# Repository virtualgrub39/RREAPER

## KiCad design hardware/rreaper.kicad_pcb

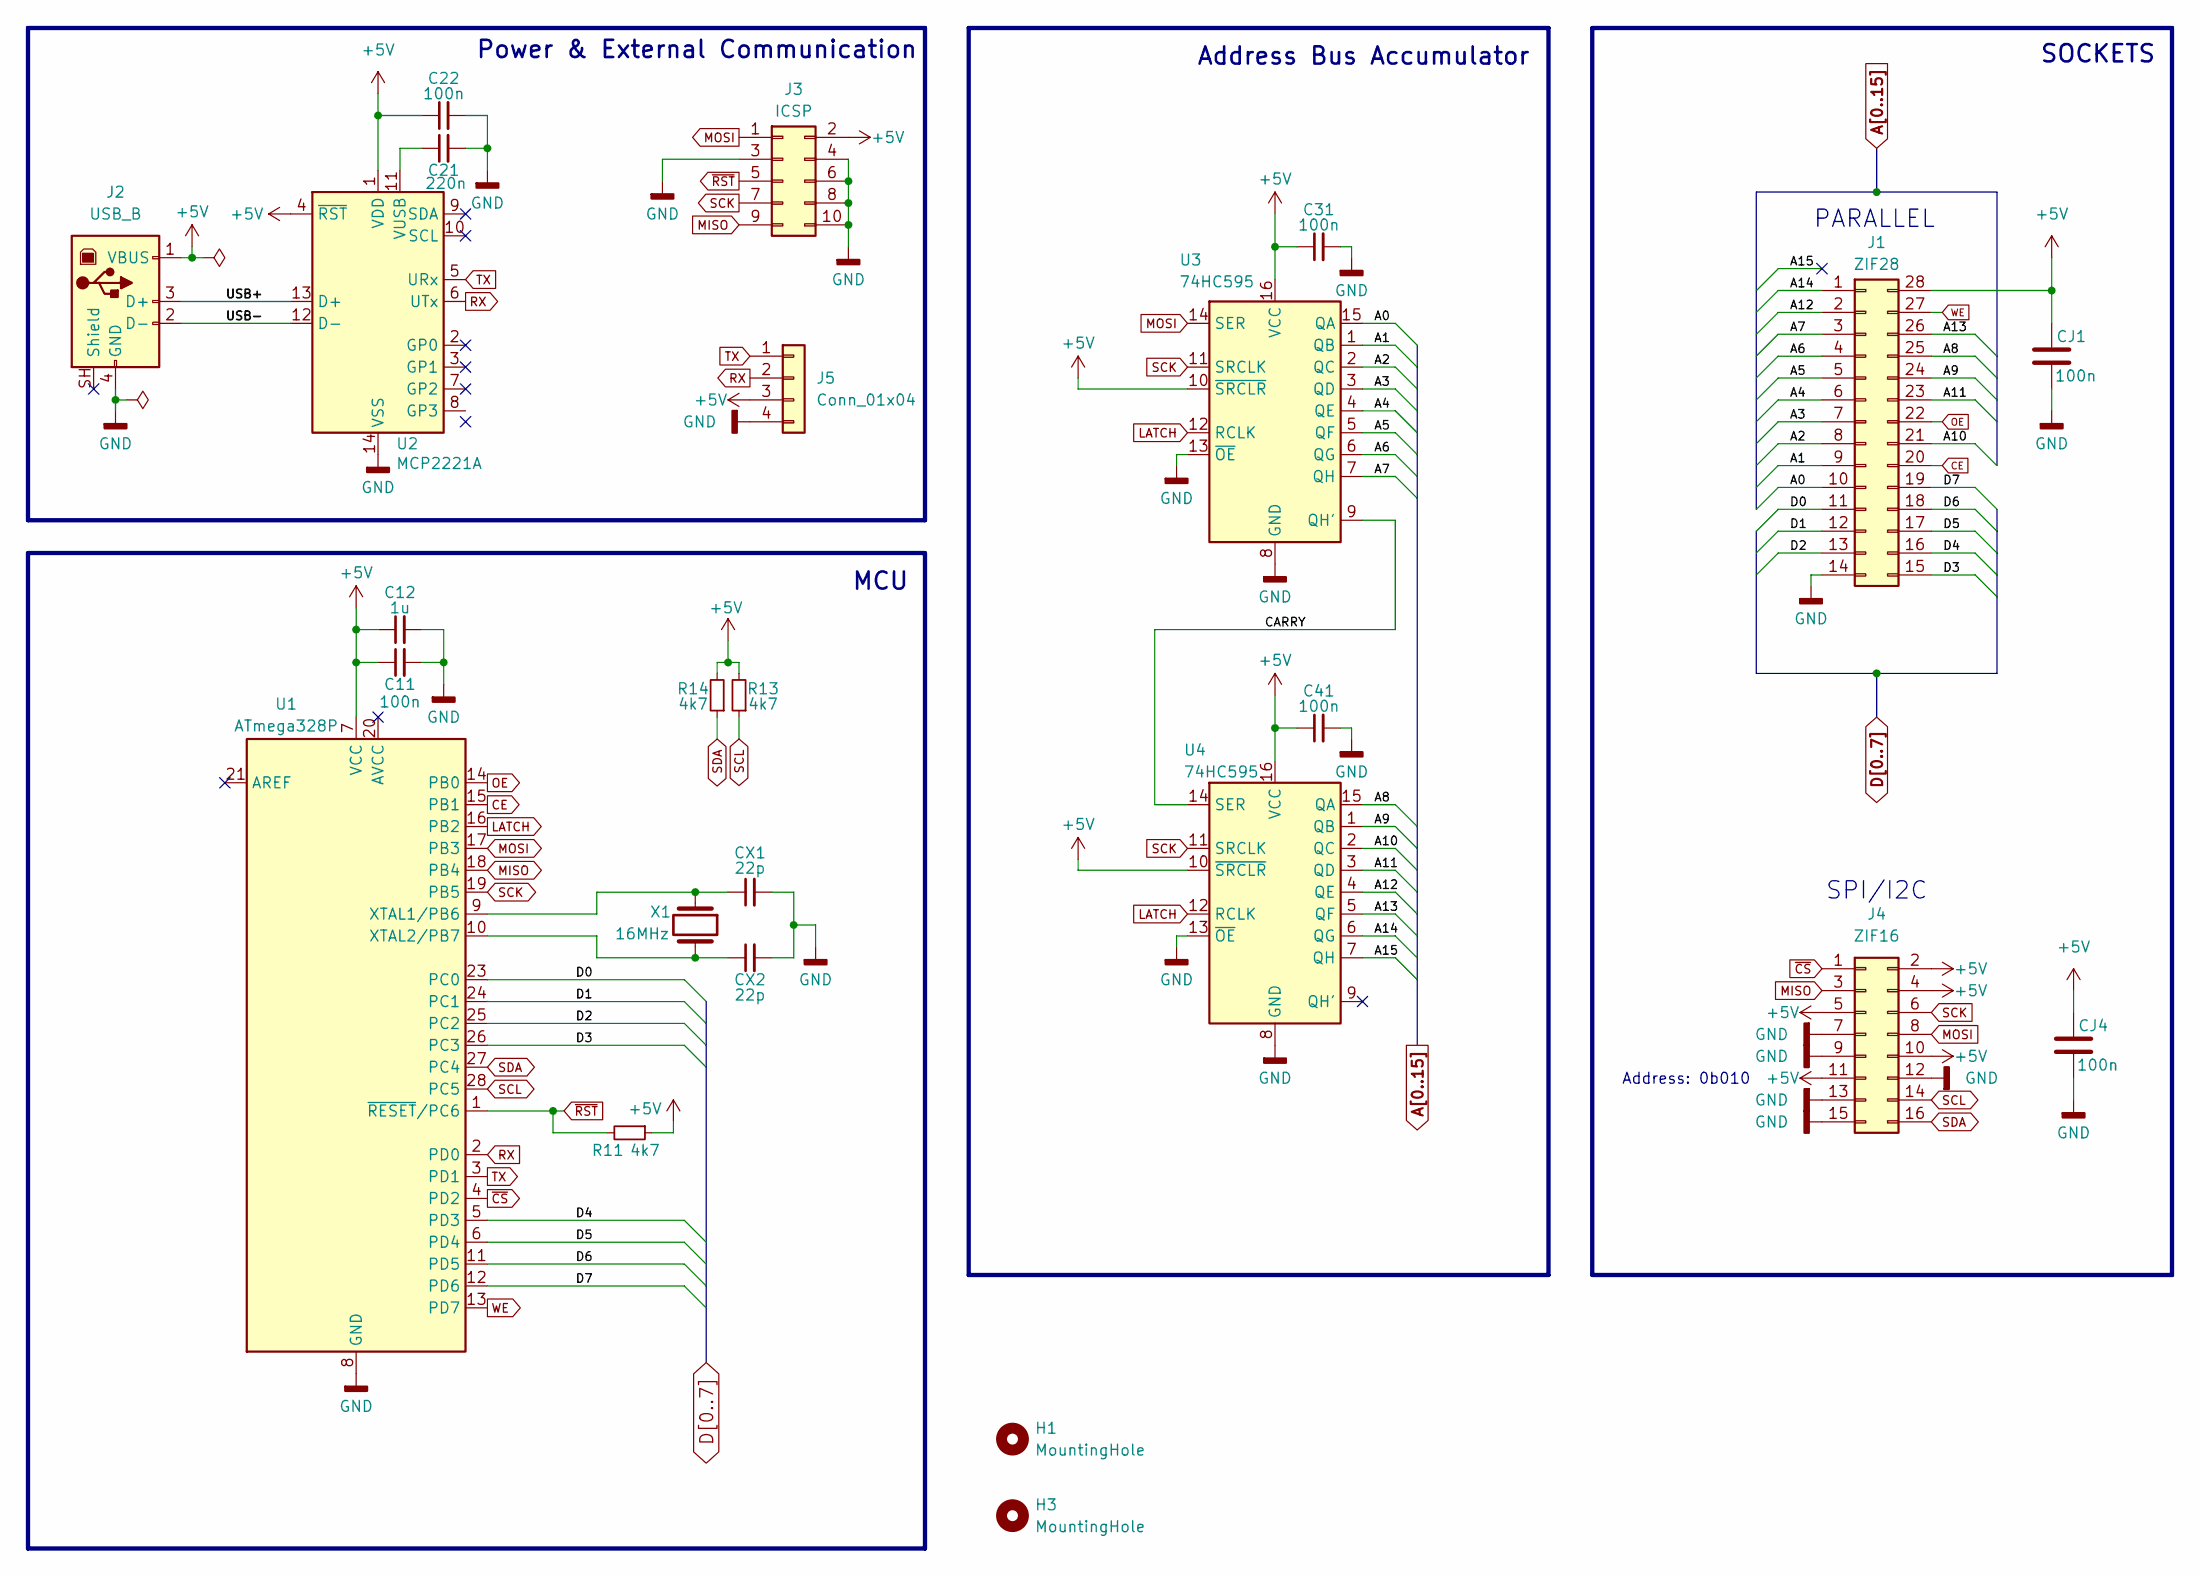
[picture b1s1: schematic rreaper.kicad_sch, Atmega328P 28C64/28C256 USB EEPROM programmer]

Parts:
C11, C22, C31, C41: 100n; C_Disc_D5.0mm_W2.5mm_P2.50mm
C12: 1u; C_Disc_D5.0mm_W2.5mm_P2.50mm
C21: 220n; C_Disc_D5.0mm_W2.5mm_P2.50mm
CJ1, CJ4: 100n; C_Disc_D5.0mm_W2.5mm_P2.50mm
CX1, CX2: 22p; C_Disc_D5.0mm_W2.5mm_P2.50mm
H1, H3: MountingHole; MountingHole_3.2mm_M3
J1: ZIF28; DIP_Socket-28_W11.9mm_W12.7mm_W15.24mm_W17.78mm_W18.5mm_3M_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
J2: USB_B; USB_B_Lumberg_2411_02_Horizontal
J3: ICSP; IDC-Header_2x05_P2.54mm_Vertical
J4: ZIF16; DIP_Socket-16_W4.3mm_W5.08mm_W7.62mm_W10.16mm_W10.9mm_3M_21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
J5: Conn_01x04; PinHeader_1x04_P2.54mm_Vertical
R11, R13, R14: 4k7; R_Axial_DIN0207_L6.3mm_D2.5mm_P7.62mm_Horizontal
U1: ATmega328P; DIP-28_W7.62mm_Socket
U2: MCP2221A; DIP-14_W7.62mm_Socket
U3, U4: 74HC595; DIP-16_W7.62mm_Socket
X1: 16MHz; Crystal_HC18-U_Vertical

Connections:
+5V: C11.1, C12.1, C22.1, C31.1, C41.1, CJ1.2, CJ4.2, J1.28, J2.1 (VBUS), J3.2, J4.2, J4.4, J4.5, J4.10, J4.11, J5.3, R11.1, R13.2, R14.2, U1.7 (VCC), U2.1 (VDD), U2.4 (~RST), U3.10 (~SRCLR), U3.16 (VCC), U4.10 (~SRCLR), U4.16 (VCC)
/CARRY: U3.9 (QH'), U4.14 (SER)
/USB+: J2.3 (D+), U2.13 (D+)
/USB-: J2.2 (D-), U2.12 (D-)
A0: J1.10, U3.15 (QA)
A1: J1.9, U3.1 (QB)
A2: J1.8, U3.2 (QC)
A3: J1.7, U3.3 (QD)
A4: J1.6, U3.4 (QE)
A5: J1.5, U3.5 (QF)
A6: J1.4, U3.6 (QG)
A7: J1.3, U3.7 (QH)
A8: J1.25, U4.15 (QA)
A9: J1.24, U4.1 (QB)
A10: J1.21, U4.2 (QC)
A11: J1.23, U4.3 (QD)
A12: J1.2, U4.4 (QE)
A13: J1.26, U4.5 (QF)
A14: J1.1, U4.6 (QG)
A15: U4.7 (QH)
CE: J1.20, U1.15 (PB1)
D0: J1.11, U1.23 (PC0)
D1: J1.12, U1.24 (PC1)
D2: J1.13, U1.25 (PC2)
D3: J1.15, U1.26 (PC3)
D4: J1.16, U1.5 (PD3)
D5: J1.17, U1.6 (PD4)
D6: J1.18, U1.11 (PD5)
D7: J1.19, U1.12 (PD6)
GND: C11.2, C12.2, C21.2, C22.2, C31.2, C41.2, CJ1.1, CJ4.1, CX1.2, CX2.2, J1.14, J2.4 (GND), J3.3, J3.4, J3.6, J3.8, J3.10, J4.7, J4.9, J4.12, J4.13, J4.15, J5.4, U1.8 (GND), U1.22 (GND), U2.14 (VSS), U3.8 (GND), U3.13 (~OE), U4.8 (GND), U4.13 (~OE)
LATCH: U1.16 (PB2), U3.12 (RCLK), U4.12 (RCLK)
MISO: J3.9, J4.3, U1.18 (PB4)
MOSI: J3.1, J4.8, U1.17 (PB3), U3.14 (SER)
unnamed: CX1.1, U1.9 (XTAL1/PB6), X1.1
unnamed: CX2.1, U1.10 (XTAL2/PB7), X1.2
unnamed: C21.1, U2.11 (VUSB)
OE: J1.22, U1.14 (PB0)
RX: J5.2, U1.2 (PD0), U2.6 (UTx)
SCK: J3.7, J4.6, U1.19 (PB5), U3.11 (SRCLK), U4.11 (SRCLK)
SCL: J4.14, R13.1, U1.28 (PC5)
SDA: J4.16, R14.1, U1.27 (PC4)
TX: J5.1, U1.3 (PD1), U2.5 (URx)
WE: J1.27, U1.13 (PD7)
~CS: J4.1, U1.4 (PD2)
~RST: J3.5, R11.2, U1.1 (~RESET/PC6)

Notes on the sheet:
Power & External Communication
PARALLEL
SPI/I2C
Address Bus Accumulator
SOCKETS
Address: 0b010
MCU

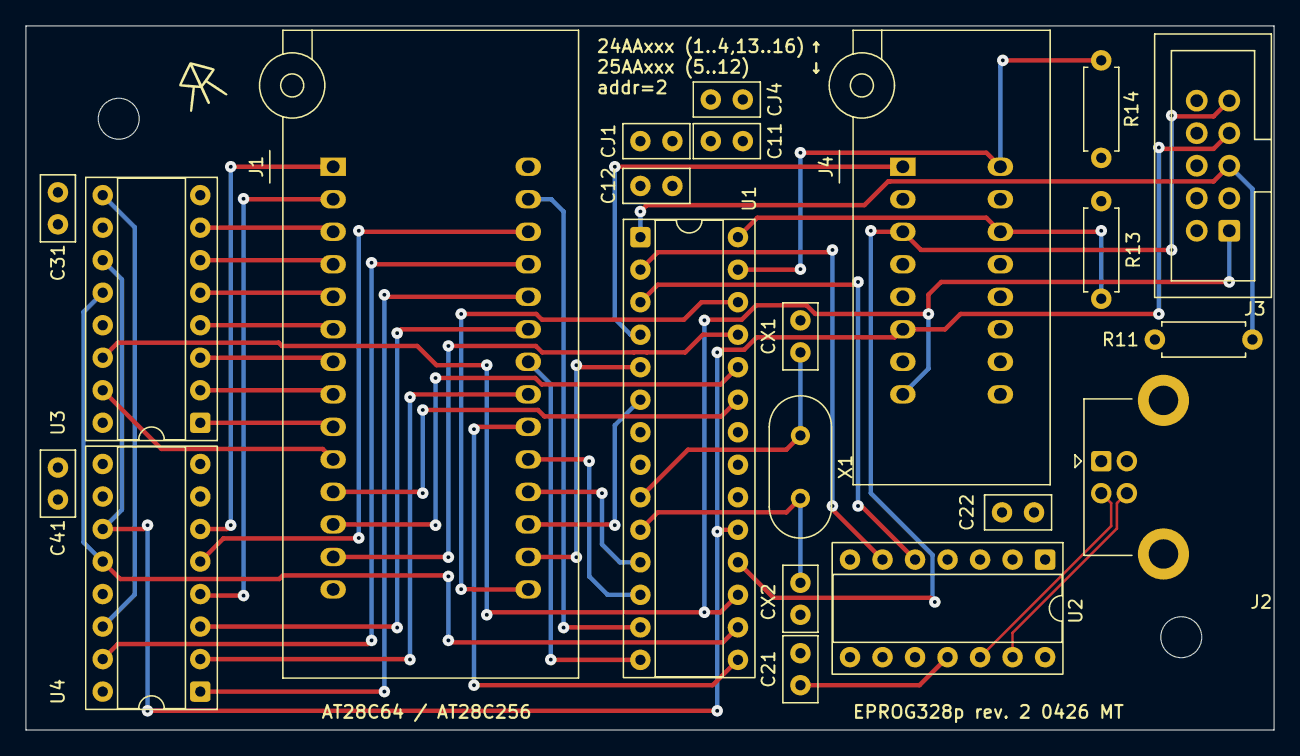
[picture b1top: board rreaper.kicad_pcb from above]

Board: 4 copper layers, 97.5 x 55.0 mm, 24 parts (0 on the bottom side), 44 nets.

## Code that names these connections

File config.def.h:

/* Copyright (C) 2026 Mikołaj Trafisz
 *
 * This file is part of RREAPER.
 * RREAPER is free software: you may redistribute it and/or modify it
 * under the terms of the GNU General Public License, version 3, or any later version.
 *
 * RREAPER comes with no warranty; see the GNU GPL for details.
 */

#ifndef CONFIG_H
#define CONFIG_H

/* serial comms */

#define BAUD 19200          // UART baud
#define TX_BUFFER_SIZE 32   // tx ring buffer size
#define RX_BUFFER_SIZE 32   // rx ring buffer size
#define STARTCODE ':'       // intel-hex start sign
#define DATA_BLOCK_SZ 16    // data block size (should fit in both tx and rx buffer for speed)

/* parallel port */

// pins used for data bus
// (PORT, NUMBER)
#define DATA_PORT   \
    X (C, 0)        \
    X (C, 1)        \
    X (C, 2)        \
    X (C, 3)        \
    X (C, 4)        \
    X (C, 5)        \
    X (D, 5)        \
    X (D, 6)

// pins used for EEPROM control
// (NAME, PORT, NUMBER)
#define CTL_PINS \
	X(CE, B, 1) \
	X(OE, B, 0) \
	X(WE, D, 7)

/* SPI shift-register */

// pins used for SPI communication
#define PORT_SPI PORTB
#define DDR_SPI DDRB
#define PIN_MOSI PB3
#define PIN_MISO PB4
#define PIN_SCK PB5
#define PIN_SS PB2

#endif

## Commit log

2026-03-28 initial
2026-03-29 cosmetic changes; added eeprom API header and placeholder implementation;
2026-03-29 1st working version; implemented the parallel-port and EEPROM API; added some docs (comments :3)
2026-03-29 licensed under GPL3; changed internal name to RREAPER;
2026-03-29 replaced flat file structure with source and include directories
2026-03-29 added verify command; added simple python driver
2026-03-29 actuall added verify command this time
2026-03-30 moved firmware into it's own directory
2026-03-30 removed bum-ass LLM python driver
2026-03-30 added base for C++/Qt UI PC driver
2026-03-31 formatted; added basic UI layout;
2026-04-03 driver: added basic state-machine
2026-04-03 added hardware directory and project files
2026-04-03 added license header to driver files
2026-04-03 added basic hardware schematic
2026-04-06 added basic PCB layout
2026-04-10 completed first PCB layout
2026-04-14 hardware: replaced USB with RS485 and external power; redesigned PCB
2026-04-16 migrated to kicad 10; added symbol for avr16dd28
2026-04-25 went back to USB; added serial eeprom socket; completed new layout
2026-04-25 basically a firmware rewrite: added CRC module and command; rewritten EEPROM module to work with multiple different device types; added device switching command; introduced more standard error / erro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
2026-04-25 added datasheets for chips used in the project; removed unused UART header from schematic
